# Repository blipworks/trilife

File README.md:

trilife
=======

Code and design files for Trilife cellular automata blinking LED project.
Initial work supported by the National Science Foundation under
Grant No. 0644511.

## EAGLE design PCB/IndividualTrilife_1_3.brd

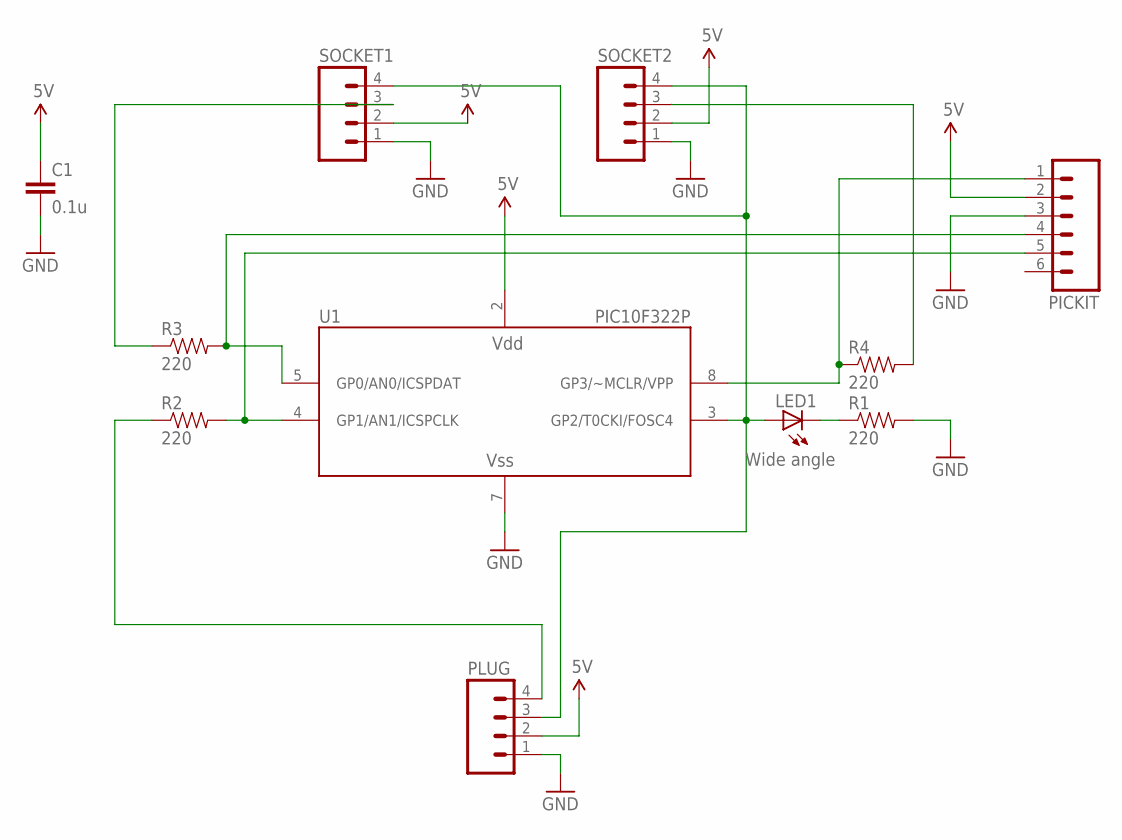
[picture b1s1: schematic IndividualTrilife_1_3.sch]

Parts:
C1: 0.1u; CAP-PTH-SMALL
LED1: Wide angle; LED5MM
PICKIT: M06LOCK; 1X06_LOCK
PLUG: M04LOCK; 1X04_LOCK
R1, R2, R3, R4: 220; AXIAL-0.4
SOCKET1, SOCKET2: M04LOCK; 1X04_LOCK
U1: PIC10F322P; DIP-8

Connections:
5V: C1.1, PICKIT.2, PLUG.2, SOCKET1.2, SOCKET2.2, U1.2 (VDD)
GND: C1.2, PICKIT.3, PLUG.1, R1.P$2 (2), SOCKET1.1, SOCKET2.1, U1.7 (VSS)
unnamed: LED1.A, PLUG.3, SOCKET1.4, SOCKET2.4, U1.3 (GP2/T0CKI/FOSC4)
unnamed: LED1.K (C), R1.P$1 (1)
unnamed: PICKIT.1, R4.P$1 (1), U1.8 (GP3/~MCLR/VPP)
unnamed: PICKIT.4, R3.P$2 (2), U1.5 (GP0/AN0/ICSPDAT)
unnamed: PICKIT.5, R2.P$2 (2), U1.4 (GP1/AN1/ICSPCLK)
unnamed: R4.P$2 (2), SOCKET2.3
unnamed: R3.P$1 (1), SOCKET1.3
unnamed: PLUG.4, R2.P$1 (1)

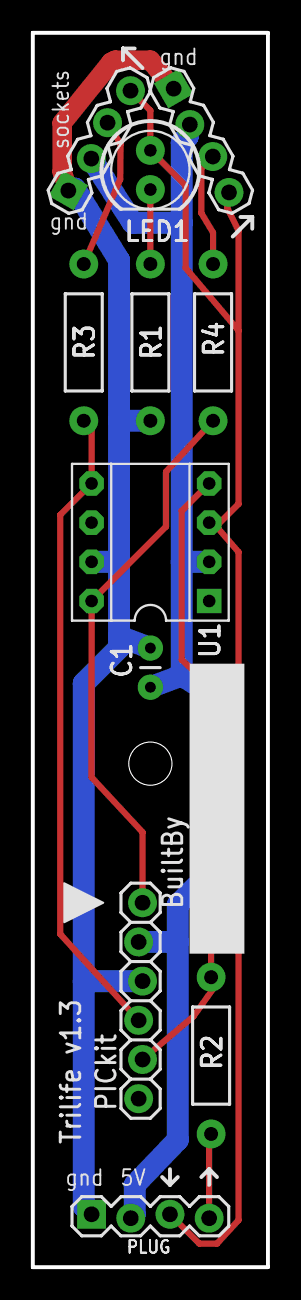
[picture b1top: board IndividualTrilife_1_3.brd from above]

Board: 2 copper layers, 15.2 x 80.0 mm, 11 parts (0 on the bottom side), 10 nets.

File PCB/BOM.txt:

Bill of Materials for Trilife Board

R1, R2, R3, R4: 220 ohm 1/4 watt resistor, Digikey 220QBK-ND

U1 PIC10F322, DigiKey PIC10F322-I/P-ND

LED Red, Kingbright 5mm dia, wide angle. Digikey 754-1564-ND, Mouser or direct from Kingbright part WP9294SEC/J3

C1 0.1 uF, 0.1" lead spacing ceramic capacitor. Adafruit product 753, Digikey 399-4151-ND or similar

Foot: #4-40x1.5 inch screw, McMaster 91772A119
Use a #4 nut if the board hole doesn't hold the screw tightly

Spacer: Nylon 1.25 inch long, 0.25 inch outer diameter, for #4 screw, McMaster 94639A210

Socket (2 pcs) 4-position 0.1" pitch right angle socket, Digikey S5479-ND
Plug (1 pc) 4-pin 0.1" pitch right angle header, Digikey 609-3319-ND




Bill of Materials for Connector Board
You need 2 of the 4-prong plugs per connector board:
4-pin 0.1" pitch right angle header, Digikey 609-3319-ND

For Power Plug Connector Board
2.1 mm jack, part CP-202-AH-ND and 2 of the 4-prong plugs 609-3319-ND

A foot and spacer are optional on the connector boards, the hole in the spacer is good for hanging up the display on a wall.

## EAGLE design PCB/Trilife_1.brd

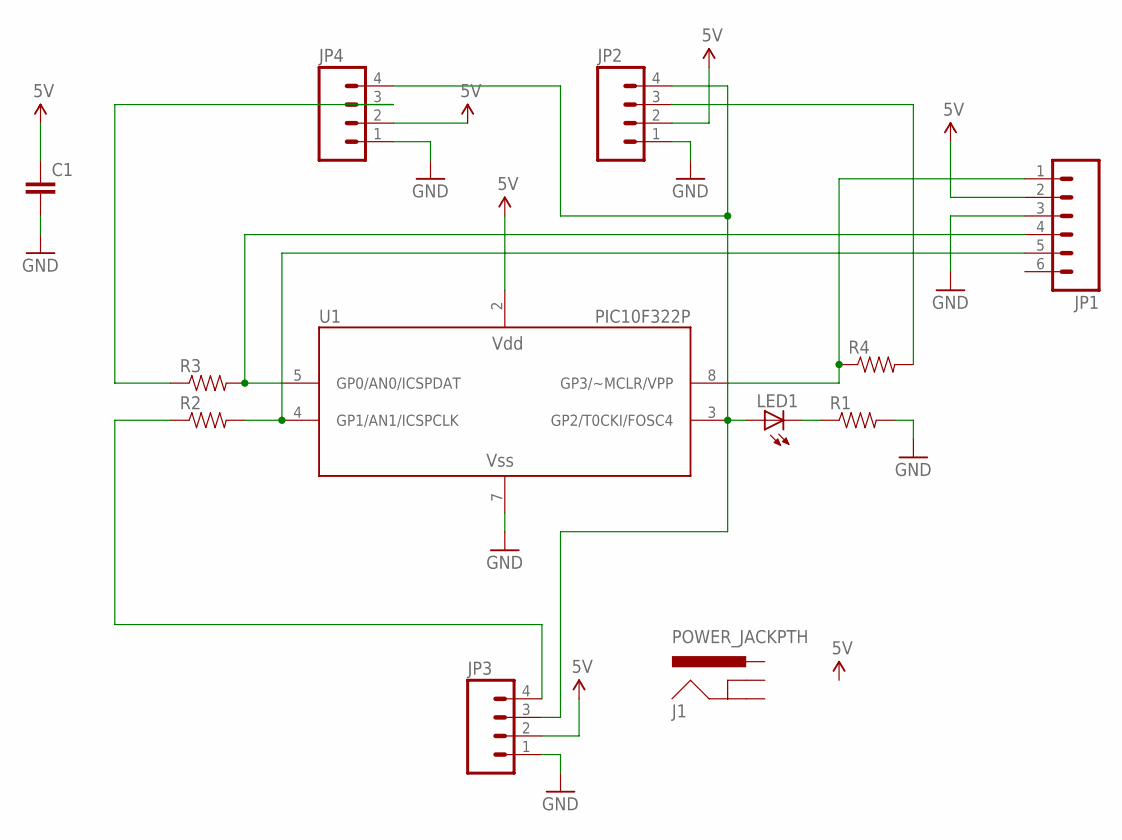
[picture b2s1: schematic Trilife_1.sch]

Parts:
C1: CAPPTH; CAP-PTH-SMALL
J1: POWER_JACKPTH; POWER_JACK_PTH
JP1: M06LOCK; 1X06_LOCK
JP2, JP3, JP4: M04LOCK; 1X04_LOCK
LED1: LED5MM
R1, R2, R3, R4: RESISTORPTH-1/4W; AXIAL-0.4
U1: PIC10F322P; DIP-8

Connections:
5V: C1.1, JP1.2, JP2.2, JP3.2, JP4.2, U1.2 (VDD)
GND: C1.2, JP1.3, JP2.1, JP3.1, JP4.1, R1.P$2 (2), U1.7 (VSS)
unnamed: JP2.4, JP3.3, JP4.4, LED1.A, U1.3 (GP2/T0CKI/FOSC4)
unnamed: LED1.K (C), R1.P$1 (1)
unnamed: JP1.1, R4.P$1 (1), U1.8 (GP3/~MCLR/VPP)
unnamed: JP1.4, R3.P$2 (2), U1.5 (GP0/AN0/ICSPDAT)
unnamed: JP1.5, R2.P$2 (2), U1.4 (GP1/AN1/ICSPCLK)
unnamed: JP2.3, R4.P$2 (2)
unnamed: JP4.3, R3.P$1 (1)
unnamed: JP3.4, R2.P$1 (1)

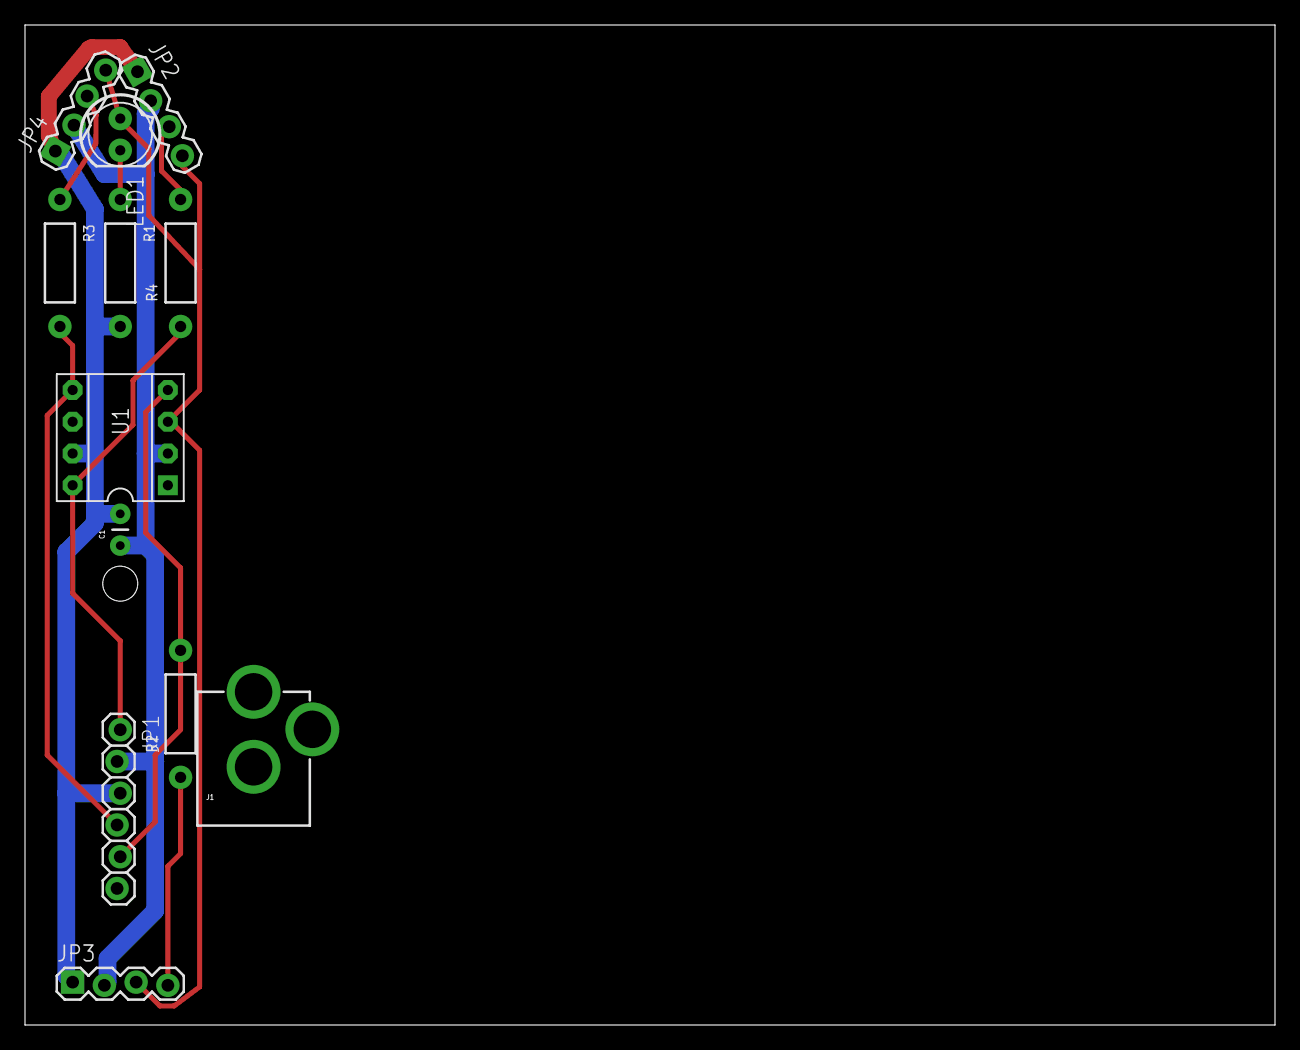
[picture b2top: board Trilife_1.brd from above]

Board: 2 copper layers, 100.0 x 80.0 mm, 12 parts (0 on the bottom side), 10 nets.

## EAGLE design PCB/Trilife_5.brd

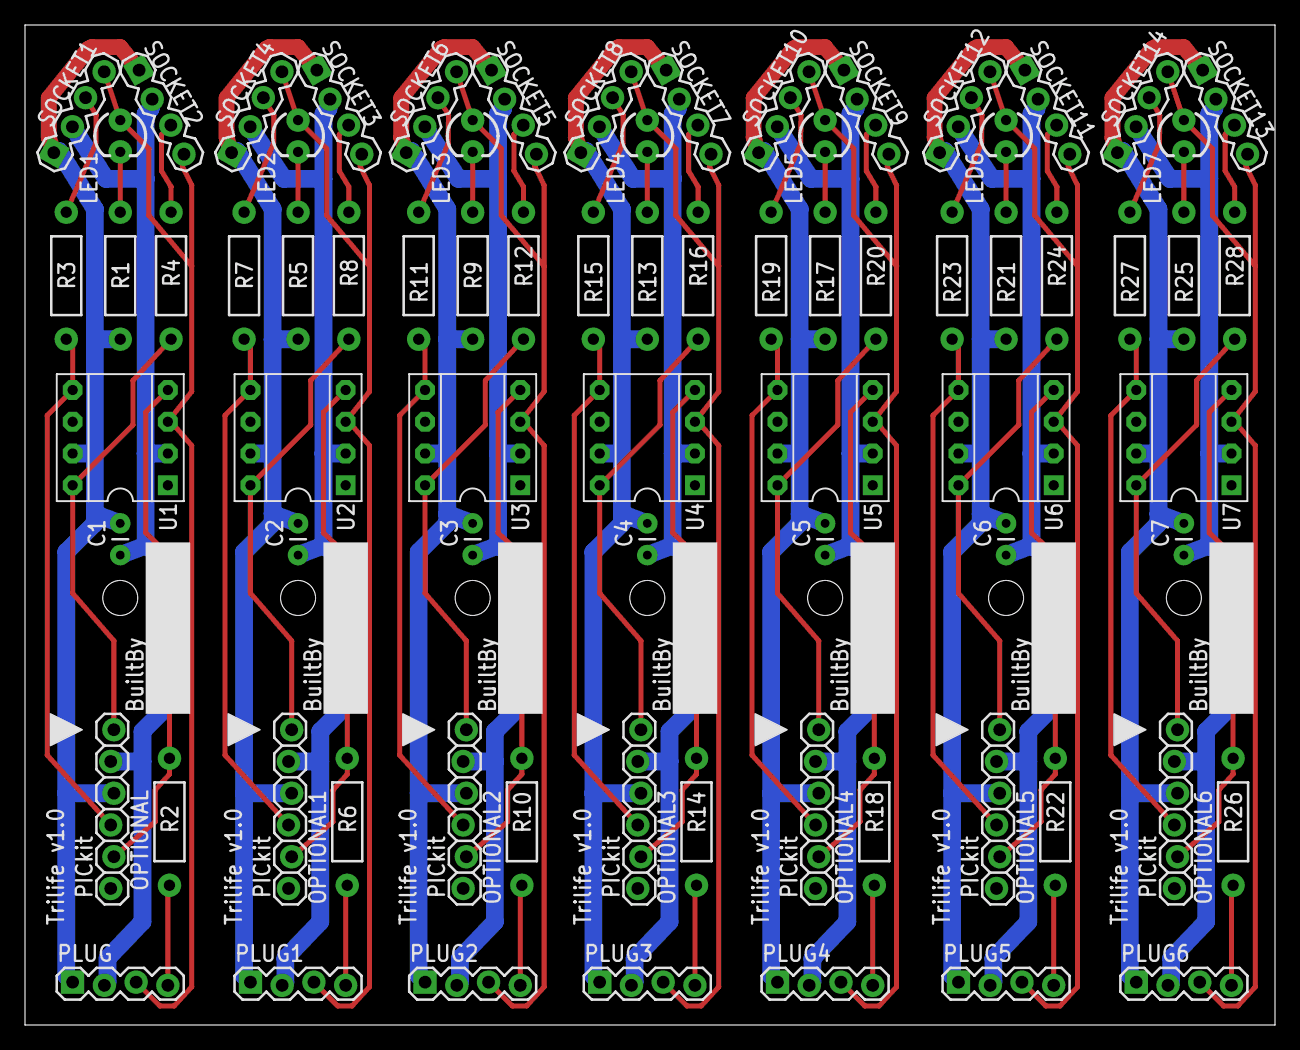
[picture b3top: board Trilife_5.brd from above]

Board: 2 copper layers, 100.0 x 80.0 mm, 77 parts (0 on the bottom side), 70 nets.

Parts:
C1, C2, C3, C4, C5, C6, C7: CAP-PTH-SMALL
LED1, LED2, LED3, LED4, LED5, LED6, LED7: LED3MM
OPTIONAL, OPTIONAL1, OPTIONAL2, OPTIONAL3, OPTIONAL4, OPTIONAL5, OPTIONAL6: 1X06_LOCK
PLUG, PLUG1, PLUG2, PLUG3, PLUG4, PLUG5, PLUG6: 1X04_LOCK
R1, R2, R3, R4, R5, R6, R7, R8, R9, R10, R11, R12, R13, R14, R15, R16, R17, R18, R19, R20, R21, R22, R23, R24, R25, R26, R27, R28: AXIAL-0.4
SOCKET1, SOCKET2, SOCKET3, SOCKET4, SOCKET5, SOCKET6, SOCKET7, SOCKET8, SOCKET9, SOCKET10, SOCKET11, SOCKET12, SOCKET13, SOCKET14: 1X04_LOCK
U1, U2, U3, U4, U5, U6, U7: PIC10F322P; DIP-8

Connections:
5V: C1.1, OPTIONAL.2, PLUG.2, SOCKET1.2, SOCKET2.2, U1.2
5V1: C2.1, OPTIONAL1.2, PLUG1.2, SOCKET3.2, SOCKET4.2, U2.2
5V2: C3.1, OPTIONAL2.2, PLUG2.2, SOCKET5.2, SOCKET6.2, U3.2
5V3: C4.1, OPTIONAL3.2, PLUG3.2, SOCKET7.2, SOCKET8.2, U4.2
5V4: C5.1, OPTIONAL4.2, PLUG4.2, SOCKET9.2, SOCKET10.2, U5.2
5V5: C6.1, OPTIONAL5.2, PLUG5.2, SOCKET11.2, SOCKET12.2, U6.2
5V6: C7.1, OPTIONAL6.2, PLUG6.2, SOCKET13.2, SOCKET14.2, U7.2
GND: C1.2, OPTIONAL.3, PLUG.1, R1.P$2, SOCKET1.1, SOCKET2.1, U1.7
GND1: C2.2, OPTIONAL1.3, PLUG1.1, R5.P$2, SOCKET3.1, SOCKET4.1, U2.7
GND2: C3.2, OPTIONAL2.3, PLUG2.1, R9.P$2, SOCKET5.1, SOCKET6.1, U3.7
GND3: C4.2, OPTIONAL3.3, PLUG3.1, R13.P$2, SOCKET7.1, SOCKET8.1, U4.7
GND4: C5.2, OPTIONAL4.3, PLUG4.1, R17.P$2, SOCKET9.1, SOCKET10.1, U5.7
GND5: C6.2, OPTIONAL5.3, PLUG5.1, R21.P$2, SOCKET11.1, SOCKET12.1, U6.7
GND6: C7.2, OPTIONAL6.3, PLUG6.1, R25.P$2, SOCKET13.1, SOCKET14.1, U7.7
unnamed: LED1.A, PLUG.3, SOCKET1.4, SOCKET2.4, U1.3
unnamed: LED1.K, R1.P$1
unnamed: OPTIONAL.1, R4.P$1, U1.8
unnamed: OPTIONAL.4, R3.P$2, U1.5
unnamed: OPTIONAL.5, R2.P$2, U1.4
unnamed: R4.P$2, SOCKET2.3
unnamed: OPTIONAL1.1, R8.P$1, U2.8
unnamed: R3.P$1, SOCKET1.3
unnamed: PLUG.4, R2.P$1
unnamed: OPTIONAL1.4, R7.P$2, U2.5
unnamed: OPTIONAL1.5, R6.P$2, U2.4
unnamed: LED2.A, PLUG1.3, SOCKET3.4, SOCKET4.4, U2.3
unnamed: LED2.K, R5.P$1
unnamed: R8.P$2, SOCKET3.3
unnamed: R7.P$1, SOCKET4.3
unnamed: PLUG1.4, R6.P$1
unnamed: OPTIONAL2.1, R12.P$1, U3.8
unnamed: OPTIONAL2.4, R11.P$2, U3.5
unnamed: OPTIONAL2.5, R10.P$2, U3.4
unnamed: LED3.A, PLUG2.3, SOCKET5.4, SOCKET6.4, U3.3
unnamed: LED3.K, R9.P$1
unnamed: R12.P$2, SOCKET5.3
unnamed: R11.P$1, SOCKET6.3
unnamed: PLUG2.4, R10.P$1
unnamed: OPTIONAL3.1, R16.P$1, U4.8
unnamed: OPTIONAL3.4, R15.P$2, U4.5
unnamed: OPTIONAL3.5, R14.P$2, U4.4
unnamed: LED4.A, PLUG3.3, SOCKET7.4, SOCKET8.4, U4.3
unnamed: LED4.K, R13.P$1
unnamed: R16.P$2, SOCKET7.3
unnamed: R15.P$1, SOCKET8.3
unnamed: PLUG3.4, R14.P$1
unnamed: OPTIONAL4.1, R20.P$1, U5.8
unnamed: OPTIONAL4.4, R19.P$2, U5.5
unnamed: OPTIONAL4.5, R18.P$2, U5.4
unnamed: LED5.A, PLUG4.3, SOCKET9.4, SOCKET10.4, U5.3
unnamed: LED5.K, R17.P$1
unnamed: R20.P$2, SOCKET9.3
unnamed: R19.P$1, SOCKET10.3
unnamed: PLUG4.4, R18.P$1
unnamed: OPTIONAL5.1, R24.P$1, U6.8
unnamed: OPTIONAL5.4, R23.P$2, U6.5
unnamed: OPTIONAL5.5, R22.P$2, U6.4
unnamed: LED6.A, PLUG5.3, SOCKET11.4, SOCKET12.4, U6.3
unnamed: LED6.K, R21.P$1
unnamed: R24.P$2, SOCKET11.3
unnamed: R23.P$1, SOCKET12.3
unnamed: PLUG5.4, R22.P$1
unnamed: OPTIONAL6.1, R28.P$1, U7.8
unnamed: OPTIONAL6.4, R27.P$2, U7.5
unnamed: OPTIONAL6.5, R26.P$2, U7.4
unnamed: LED7.A, PLUG6.3, SOCKET13.4, SOCKET14.4, U7.3
unnamed: LED7.K, R25.P$1
unnamed: R28.P$2, SOCKET13.3
unnamed: R27.P$1, SOCKET14.3
unnamed: PLUG6.4, R26.P$1

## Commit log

2012-04-29 Created gh-pages branch via GitHub
2012-05-04 Added link to movie of bigger array
2012-05-18 Updated BuildingTrilife to show a bigger array
2012-05-18 updated link to video of a larger trilife array
2012-09-24 Updated with improved LED silkscreen and added connector and power boards
2012-09-24 Updated code to randomize and restart if a pattern has not formed
2012-09-24 Added pattern for a triangular paper light diffuser
2012-09-24 Added some info about simulating Trilife using JCASIM, www.jcasim.de
2012-09-24 Link to new video showing triangle paper pixels
2012-09-24 Link to new video with triangle paper pixels
2012-09-24 Added poster for OHS 2012
2013-07-29 Updated link to a larger 92-board video
2013-07-29 fix typo
2013-07-29 Rename README.md to index.html
2013-07-29 Rename index.html to README.md
2013-07-29 fix typo!
2013-07-29 make video loop

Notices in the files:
parts and their libraries:
SparkFun: Licensing: CC v3.0 Share-Alike You are welcome to use this library for commercial purposes.
